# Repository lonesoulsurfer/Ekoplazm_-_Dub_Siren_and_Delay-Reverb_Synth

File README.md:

# Ekoplazm - Dub Siren and Delay-Reverb Synth

This is my 3rd instalment in the ‘Little synths with BIG sound’ series.

This time around I’ve designed a 2 in 1 synth which I've called Ekoplazm! The first synth is a classic Dub Siren which I have paired up with a Delay and Reverb synth and includes feedback and a couple other tricks. You can play the Dub Siren through the Delay/Reverb section which gives it a rich and full sound or play other synths like my Proton & Elements synths through the Delay/Reverb section to add some tasty soundscapes to these synths.

Instructables step by step guide: https://www.instructables.com/Dub-Siren-DelayReverb-2-in-1-Synth-Little-Synths-W/

Youtube vid: https://www.youtube.com/watch?v=j3549u53hR0&source_ve_path=Mjg2NjY

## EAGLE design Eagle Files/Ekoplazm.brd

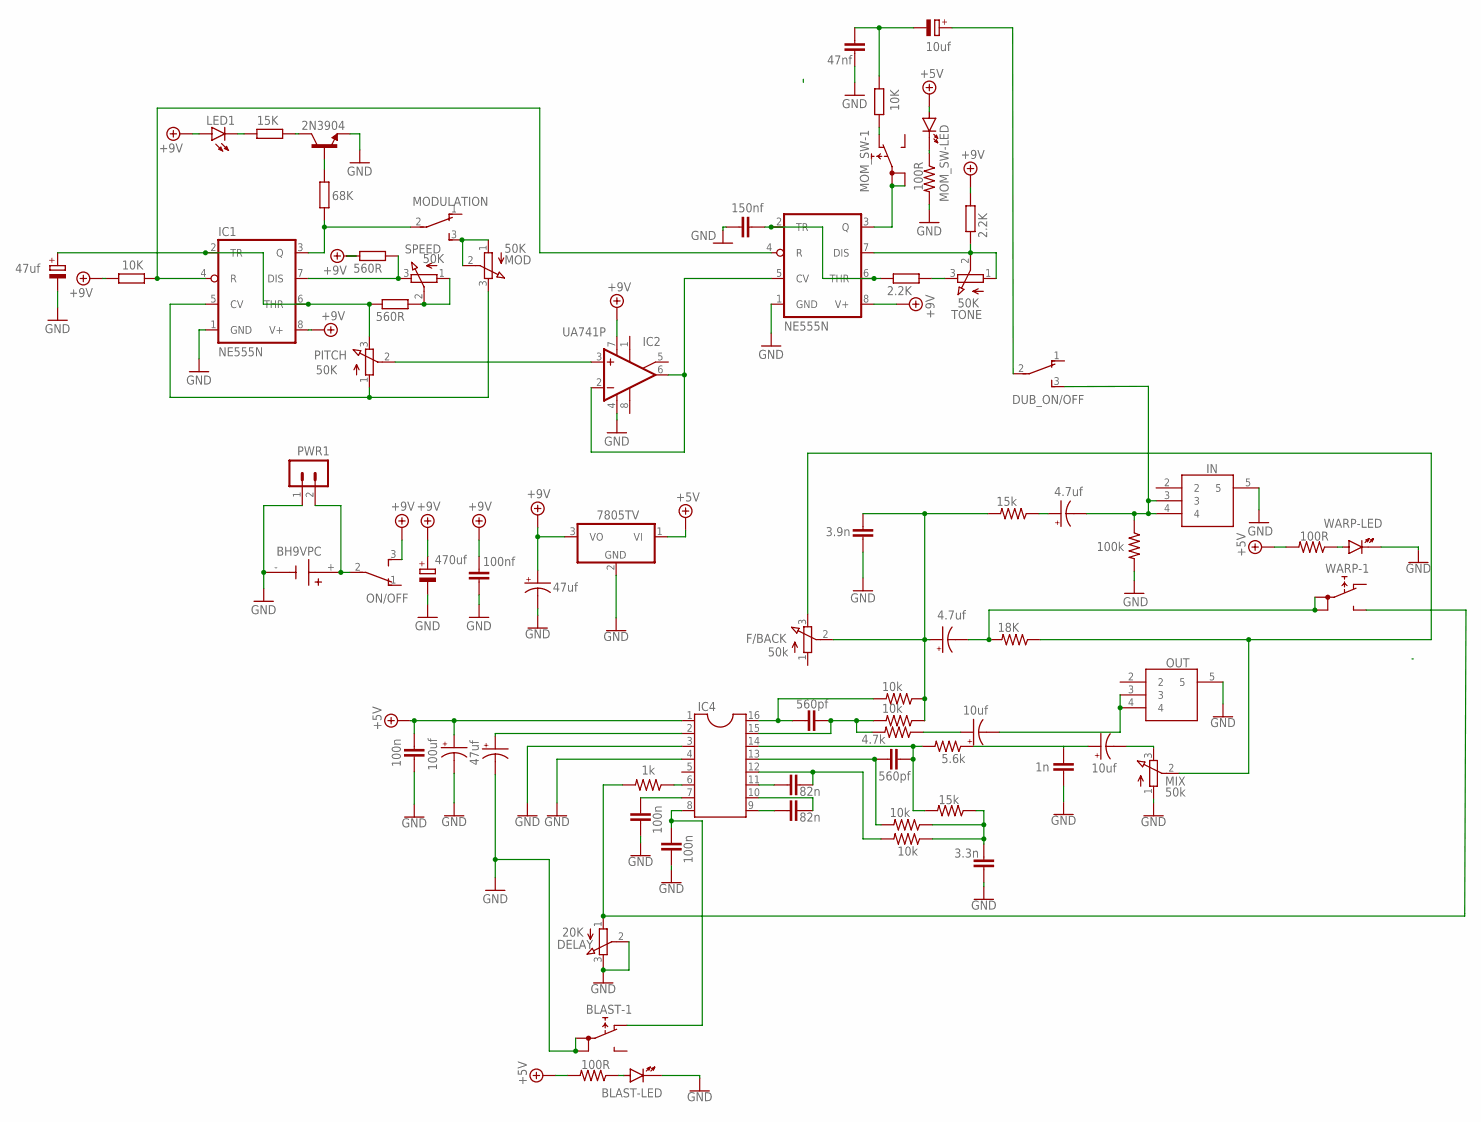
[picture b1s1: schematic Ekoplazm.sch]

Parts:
10K: 10K; 0207/10
BLAST: 5501-1LED
BT1: BH9VPC; BAT_BH9VPC
C1, C7, C14: 47uf; E2-5
C2: 470uf; E3,5-8
C3: 100nf; C050-024X044
C4: 150nf; C050-024X044
C5: 47nf; C050-024X044
C6, C18, C20: 10uf; E2-5
C8: 1n; C050-024X044
C9, C10, C11: 100n; C050-024X044
C12, C15: 82n; C050-024X044
C13: 100uf; E2-5
C16, C17: 560pf; C050-024X044
C19: 3.3n; C050-024X044
C21, C23: 4.7uf; E2-5
C22: 3.9n; C050-024X044
DELAY: 20K; EVUFXL
DUB_ON/OFF: TL36PO; TL3XPO
F/BACK: 50k; EVUFXL
IC1, IC3: NE555N; DIL08
IC2: UA741P; DIL08
IC4: DIL16
IC5: 7805TV; TO220V
IN: PJ-320A; PJ320A
LED1: LED3MM
MIX: 50k; EVUFXL
MOD: 50K; EVUF
MODULATION: TL36PO; TL3XPO
MOM_SW: 5501-1LED
ON/OFF: TL36PO; TL3XPO
OUT: PJ-320A; PJ320A
PITCH: 50K; EVUF
PWR1: B2B-PH-K-S
R1: 10K; 0207/10
R2, R7: 560R; 0207/10
R3: 68K; 0207/10
R4: 15K; 0207/10
R5, R6: 2.2K; 0207/10
R8, R12, R15, R17: 10k; 0207/10
R10: 5.6k; 0207/10
R11: 1k; 0207/10
R13, R19: 15k; 0207/10
R14, R21, R22: 100R; 0207/10
R16: 4.7k; 0207/10
R18: 18K; 0207/10
R20: 100k; 0207/10
SPEED: 50K; EVUF
T1: 2N3904; TO92
TONE: 50K; EVUF
WARP: 5501-1LED

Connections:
+5V: C9.1, C13.+, IC4.1, IC5.1 (VI), MOM_SW.+ (A), R14.2, R22.2
+9V: C2.+, C3.1, C14.+, IC1.8 (V+), IC2.7 (V+), IC3.8 (V+), IC5.3 (VO), LED1.A, ON/OFF.3 (S), R1.1, R6.2, R7.1
GND: BLAST.1A, BLAST.1B, BLAST.- (K), BT1.-, C1.-, C2.-, C3.2, C4.1, C5.1, C7.-, C8.2, C9.2, C10.2, C11.2, C13.-, C14.-, C19.1, C22.2, DELAY.2 (S), DELAY.3 (E), IC1.1 (GND), IC2.4 (V-), IC3.1 (GND), IC4.3, IC4.4, IC5.2 (GND), IN.5, MIX.1 (A), OUT.5, PWR1.1, R20.2, R21.2, T1.3 (E), WARP.- (K)
unnamed: C1.+, IC1.2 (TR), IC1.6 (THR), PITCH.3 (E), R2.1
unnamed: R2.2, SPEED.1 (A), SPEED.2 (S)
unnamed: IC1.7 (DIS), R7.2, SPEED.3 (E)
unnamed: IC1.5 (CV), MOD.3 (E), PITCH.1 (A)
unnamed: IC1.4 (R), IC3.4 (R), R1.2
unnamed: R3.2, T1.2 (B)
unnamed: R4.1, T1.1 (C)
unnamed: LED1.K (C), R4.2
unnamed: IC1.3 (Q), MODULATION.2, R3.1
unnamed: MOD.1 (A), MOD.2 (S), MODULATION.3 (S)
unnamed: BT1.+, ON/OFF.2, PWR1.2
unnamed: IC2.3 (+IN), PITCH.2 (S)
unnamed: IC2.2 (-IN), IC2.6 (OUT), IC3.5 (CV)
unnamed: C4.2, IC3.2 (TR), IC3.6 (THR), R5.1
unnamed: R5.2, TONE.3 (E)
unnamed: IC3.7 (DIS), R6.1, TONE.1 (A), TONE.2 (S)
unnamed: C7.+, IC4.2
unnamed: 10K.2, C5.2, C6.-
unnamed: C6.+, DUB_ON/OFF.2
unnamed: MOM_SW.- (K), R21.1
unnamed: IC4.6, R11.1
unnamed: C10.1, IC4.7
unnamed: C12.1, IC4.9
unnamed: C12.2, IC4.10
unnamed: C15.1, IC4.11
unnamed: C15.2, IC4.12, R8.2
unnamed: C19.2, R8.1, R12.1, R13.1
unnamed: C16.1, IC4.13, R12.2
unnamed: C16.2, IC4.14, R10.2, R13.2
unnamed: C8.1, C18.+, R10.1
unnamed: C20.+, R16.1
unnamed: C17.1, IC4.16, R17.2
unnamed: C17.2, IC4.15, R15.2, R16.2
unnamed: C21.+, C22.1, F/BACK.2 (S), R15.1, R17.1, R19.2
unnamed: C21.-, R18.2, WARP.1A, WARP.1B
unnamed: F/BACK.3 (E), MIX.2 (S), R18.1
unnamed: C23.+, R19.1
unnamed: C23.-, DUB_ON/OFF.3 (S), IN.3, IN.4, R20.1
unnamed: IC3.3 (Q), MOM_SW.1A, MOM_SW.1B
unnamed: DELAY.1 (A), R11.2, WARP.NO
unnamed: 10K.1, MOM_SW.NC
unnamed: BLAST.NC, C11.1, IC4.8
unnamed: BLAST.+ (A), R14.1
unnamed: C20.-, OUT.3, OUT.4
unnamed: C18.-, MIX.3 (E)
unnamed: R22.1, WARP.+ (A)

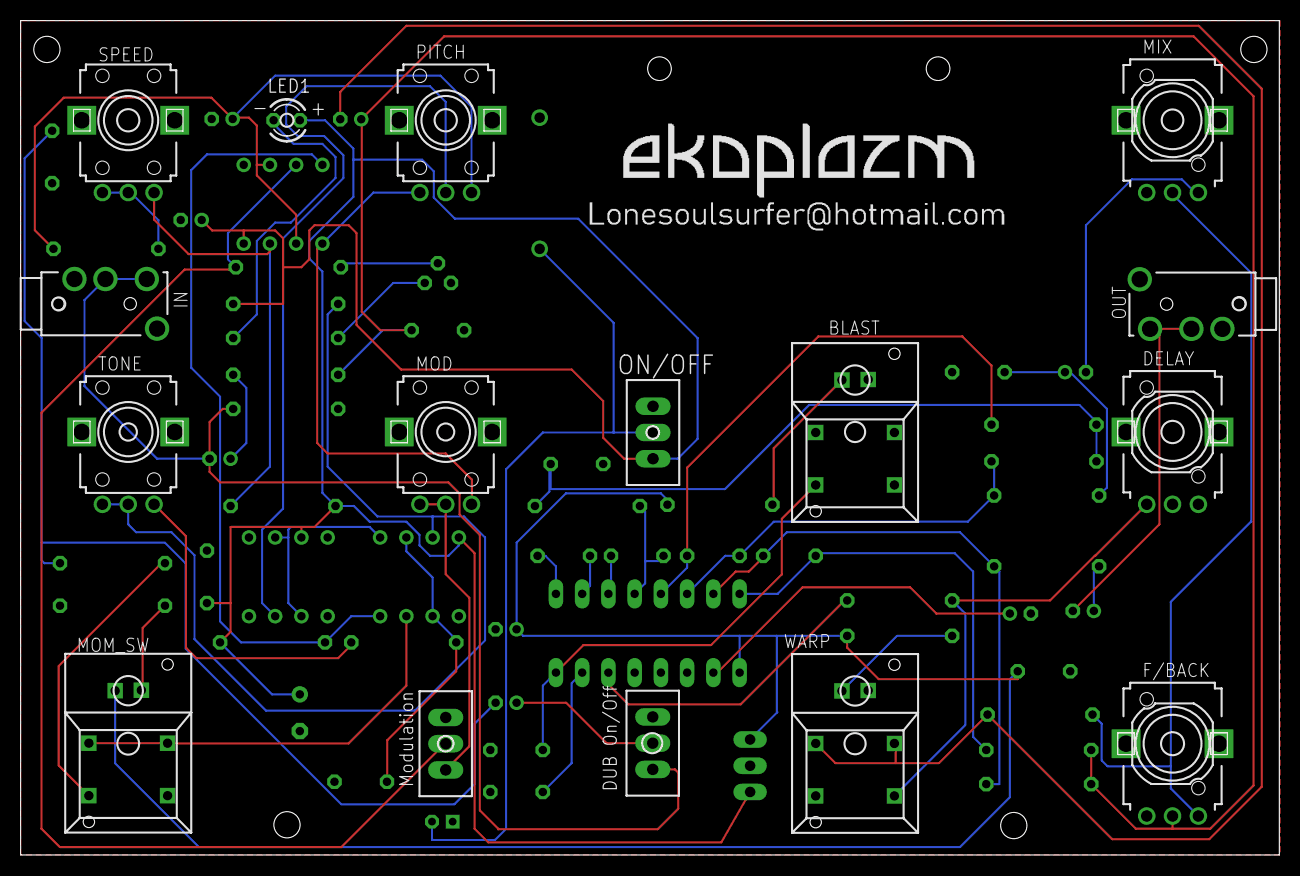
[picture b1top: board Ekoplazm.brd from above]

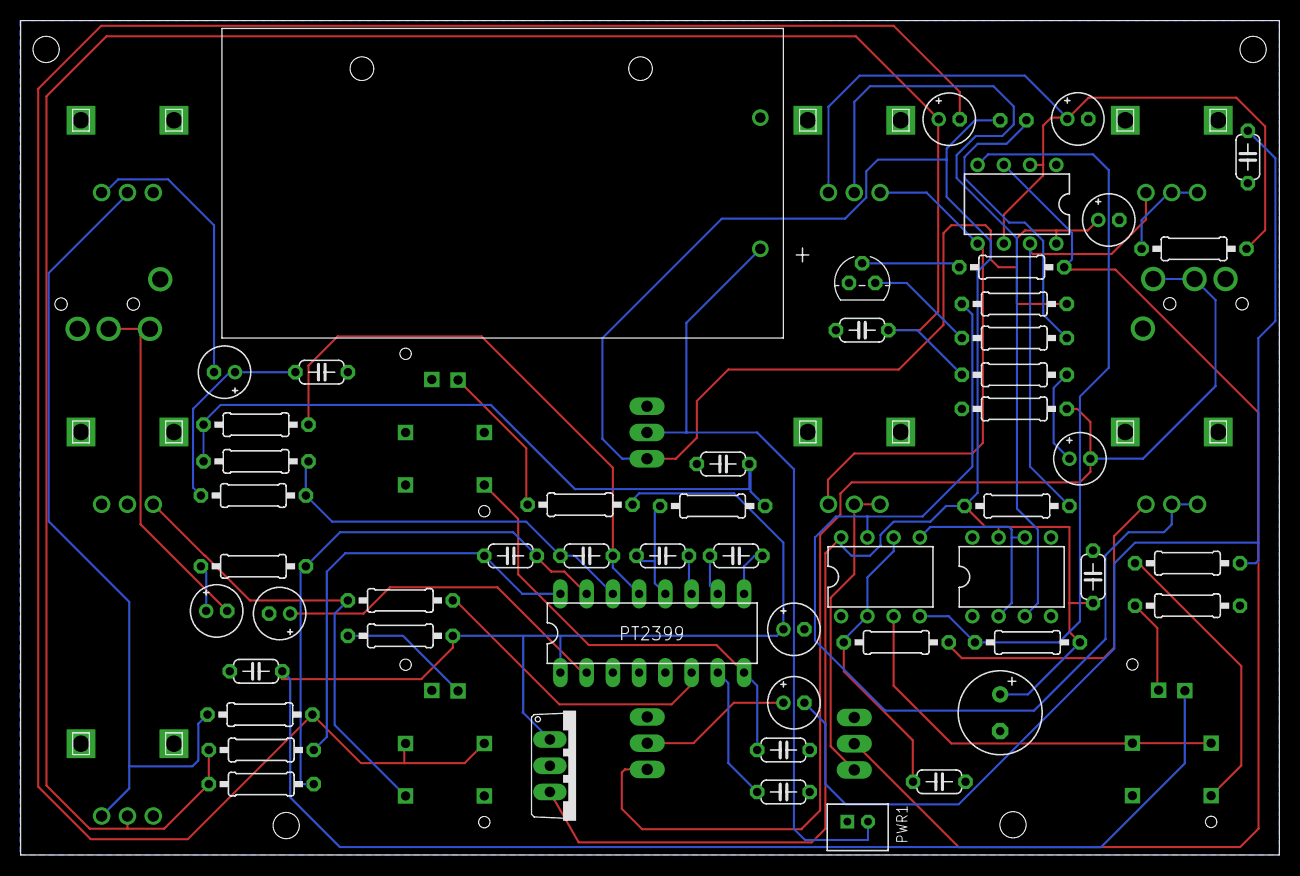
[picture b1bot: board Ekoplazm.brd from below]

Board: 2 copper layers, 121.8 x 80.8 mm, 69 parts (53 on the bottom side), 49 nets.

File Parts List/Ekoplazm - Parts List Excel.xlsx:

Part | Type | Value | Qty | Part Name | Link | Image
Switches | Momentary |  | 3 | PB86-A1/A0 | Link
 | Toggle |  | 3 | Through hole version | Link
Battery Holder | 9V |  | 1 | BH9VPC | Link
Capacitor | Polarized | 4.7uf | 2 |  | Link
 |  | 47uf | 3
 |  | 470uf | 1
 |  | 10uf | 2
 |  | 100uf | 1
 | Polyester | 100nf | 4 |  | Link
 |  | 150nf | 1
 |  | 47nf | 1
 |  | 1nf | 1
 |  | 82nf | 2
 |  | 3.3nf | 1
 |  | 3.9nf | 1
 | Ceramic | 560pf | 2 |  | Link
Potentiometer | 9 mm vertical | 20K | 1 |  | Link
 |  | 50K | 7
IC's | 555 |  | 2 |  | Link
 | 741 | op amp | 1 |  | Link
 | PT2399 |  | 1 |  | Link
Voltage regulator | 7805 |  | 1 |  | Link
3.5 mm Audio Jack Connector |  |  | 2 | PJ320A | Link
LED | 3mm |  | 1 |  | Link
JST PH Series Connector |  |  | 1 | B2B-PH-K-S | Link
Resistor | Metal Film | 10K | 6 |  | Link
 |  | 560R | 2
 |  | 68K | 1
 |  | 15K | 3
 |  | 2.2K | 2
 |  | 5.6k | 1
 |  | 1k | 1
 |  | 100R | 3
 |  | 4.7K | 1
 |  | 18K | 1
 |  | 100K | 1
Transistor | 2N3904 |  | 1 |  | Link

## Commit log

2024-12-26 File

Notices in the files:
parts and their libraries:
SparkFun-PowerSymbols: Licensing: Creative Commons ShareAlike 4.0 International - https://creativecommons.org/licenses/by-sa/4.0
